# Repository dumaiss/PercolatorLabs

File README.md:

# Percolator Labs

**Homebrew Multimedia Cards for Retro Coffee-Themed Computers**

## About Percolator Labs

Percolator Labs is a collection of custom multimedia expansion cards (graphics and audio) designed for the **pBITz** series of homebrew retro computers.

Just like a perfect cup of coffee, these cards deliver rich visuals, deep sound, and satisfying performance — freshly brewed on the hardware bus.

**Tagline:**  
**"Brewed Pixels. Brewed Beats. One Perfect Cup."**

## Philosophy

- **Thematic Consistency**: Every card name follows a coffee hierarchy, from simple drip to complex crafted experiences.
- **Progressive Enhancement**: Cards scale in capability matching the host machines — from Z80 classics to 68k powerhouses.
- **Homebrew Spirit**: Designed for fun, experimentation, and maximum retro enjoyment.

---

These cards are designed specifically for the **pBITz** series of coffee-themed homebrew machines.

## Percolator Pixel — Graphics Cards

**Series Tagline:** "Freshly Rendered Graphics"

| Card | Name                        | Hardware Highlights                                      | Recommended For          | Tagline                                      |
|------|-----------------------------|----------------------------------------------------------|--------------------------|----------------------------------------------|
| 0    | **Virtual Drip**            |  Virtual TMS9928A via serial + RFB server                | Development / All        | "All the flavor, zero hardware."             |
| 1    | **Morning Joe**             | TMS9928A base implementation                             | Zephyr-80                | "The honest classic. No froth, just pure video." |
| 2    | **Lunch Crema**             | V9958 + 192KiB RAM                                       | Zephyr-80 / Espresso-09  | "Rich. Smooth. Upgraded."                    |
| 3    | **Afternoon Latte**         | Custom tile engine, 512KiB RAM, RX660 coprocessor, HD6445 CRTC, 640×480 256c | Espresso-09     | "Precision-crafted visuals."                 |
| 4    | **Nightly Double Shot**     | Framebuffer VDP, 2MiB RAM, RX660 coprocessor, HD63484 ACRTC, 1024×768 256c | Ristretto-68 / Nitro-30 | "Heavy caffeine for your framebuffer."       |

## Percolator Audio — Sound Cards

**Series Tagline:** "Brewed Beats"

| Card | Name                   | Hardware Highlights                                           | Recommended For          | Tagline                                           |
|------|------------------------|---------------------------------------------------------------|--------------------------|---------------------------------------------------|
| 0    | **Virtual Drip**       | Virtual SN76489 (3 voices + noise) via serial proxy          | Development / All        | "All the tone, zero silicon."                     |
| 1    | **Early Roast**        | 4× real SN76489 chips + PCM channel                          | Zephyr-80 / Espresso-09  | "Four classic chips, one pure shot."              |
| 2    | **Midday Blend**       | Yamaha real chip?                                            | Mid-range machines       | "Thick, rich, and layered."                       |
| 3    | **Twilight Mocha Mix** | Coprocessor-backed engine: up to 8 channels / 3-op FM + PCM  | Ristretto-68 / Nitro-30  | "Coprocessor-crafted audio art."                  |

## Roadmap

- **Phase 1 (Current)**: Core card designs (Virtual Drip, Original Joe, Crema/Latte Art, Double Shot / Quad Crema / Latte Symphony)
- **Phase 2**: Complete schematics, KiCad files, and firmware for all cards
- **Phase 3**: Driver development for Nitros-9, custom OS on 68k machines, and demo software
- **Phase 4**: Full documentation, programming manuals, and artwork (stickers, faceplates)
- **Phase 5**: Community releases, possible physical runs, and expansion ideas (e.g. higher-res cards, MIDI, etc.)

## Project Goals

- Create a cohesive multimedia ecosystem for homebrew 8/16-bit machines.
- Maintain strong coffee + retro computing theming.
- Provide high-quality, well-documented hardware and software interfaces.
- Encourage community contributions and forks.

## Repository Structure (Planned)

```
Percolator-Labs/
├── docs/                  # Schematics, manuals, programming guides
├── hardware/
│   ├── pixel/             # Graphics card designs
│   └── audio/             # Sound card designs
├── firmware/              # FPGA code, drivers
├── software/              # OS drivers (Nitros-9, custom OS, etc.)
├── artwork/               # Logos, stickers, silkscreens
└── README.md
```

## Getting Started

1. Browse the `hardware/` directory for schematics and KiCad files.
2. Check `docs/` for card-specific programming manuals.
3. Join the discussion on your favorite retro forum (or open an Issue here).

## License

This is a homebrew / open hardware project. All designs are released under the **Creative Commons Attribution-ShareAlike 4.0** license unless otherwise noted.

---

**Brewed with passion in the home lab.**  
☕ **Percolator Labs** — Making retro computing taste better since 2026.

---

*Last updated: June 2026*  
*Made for the pBITz family of homebrew machines.*

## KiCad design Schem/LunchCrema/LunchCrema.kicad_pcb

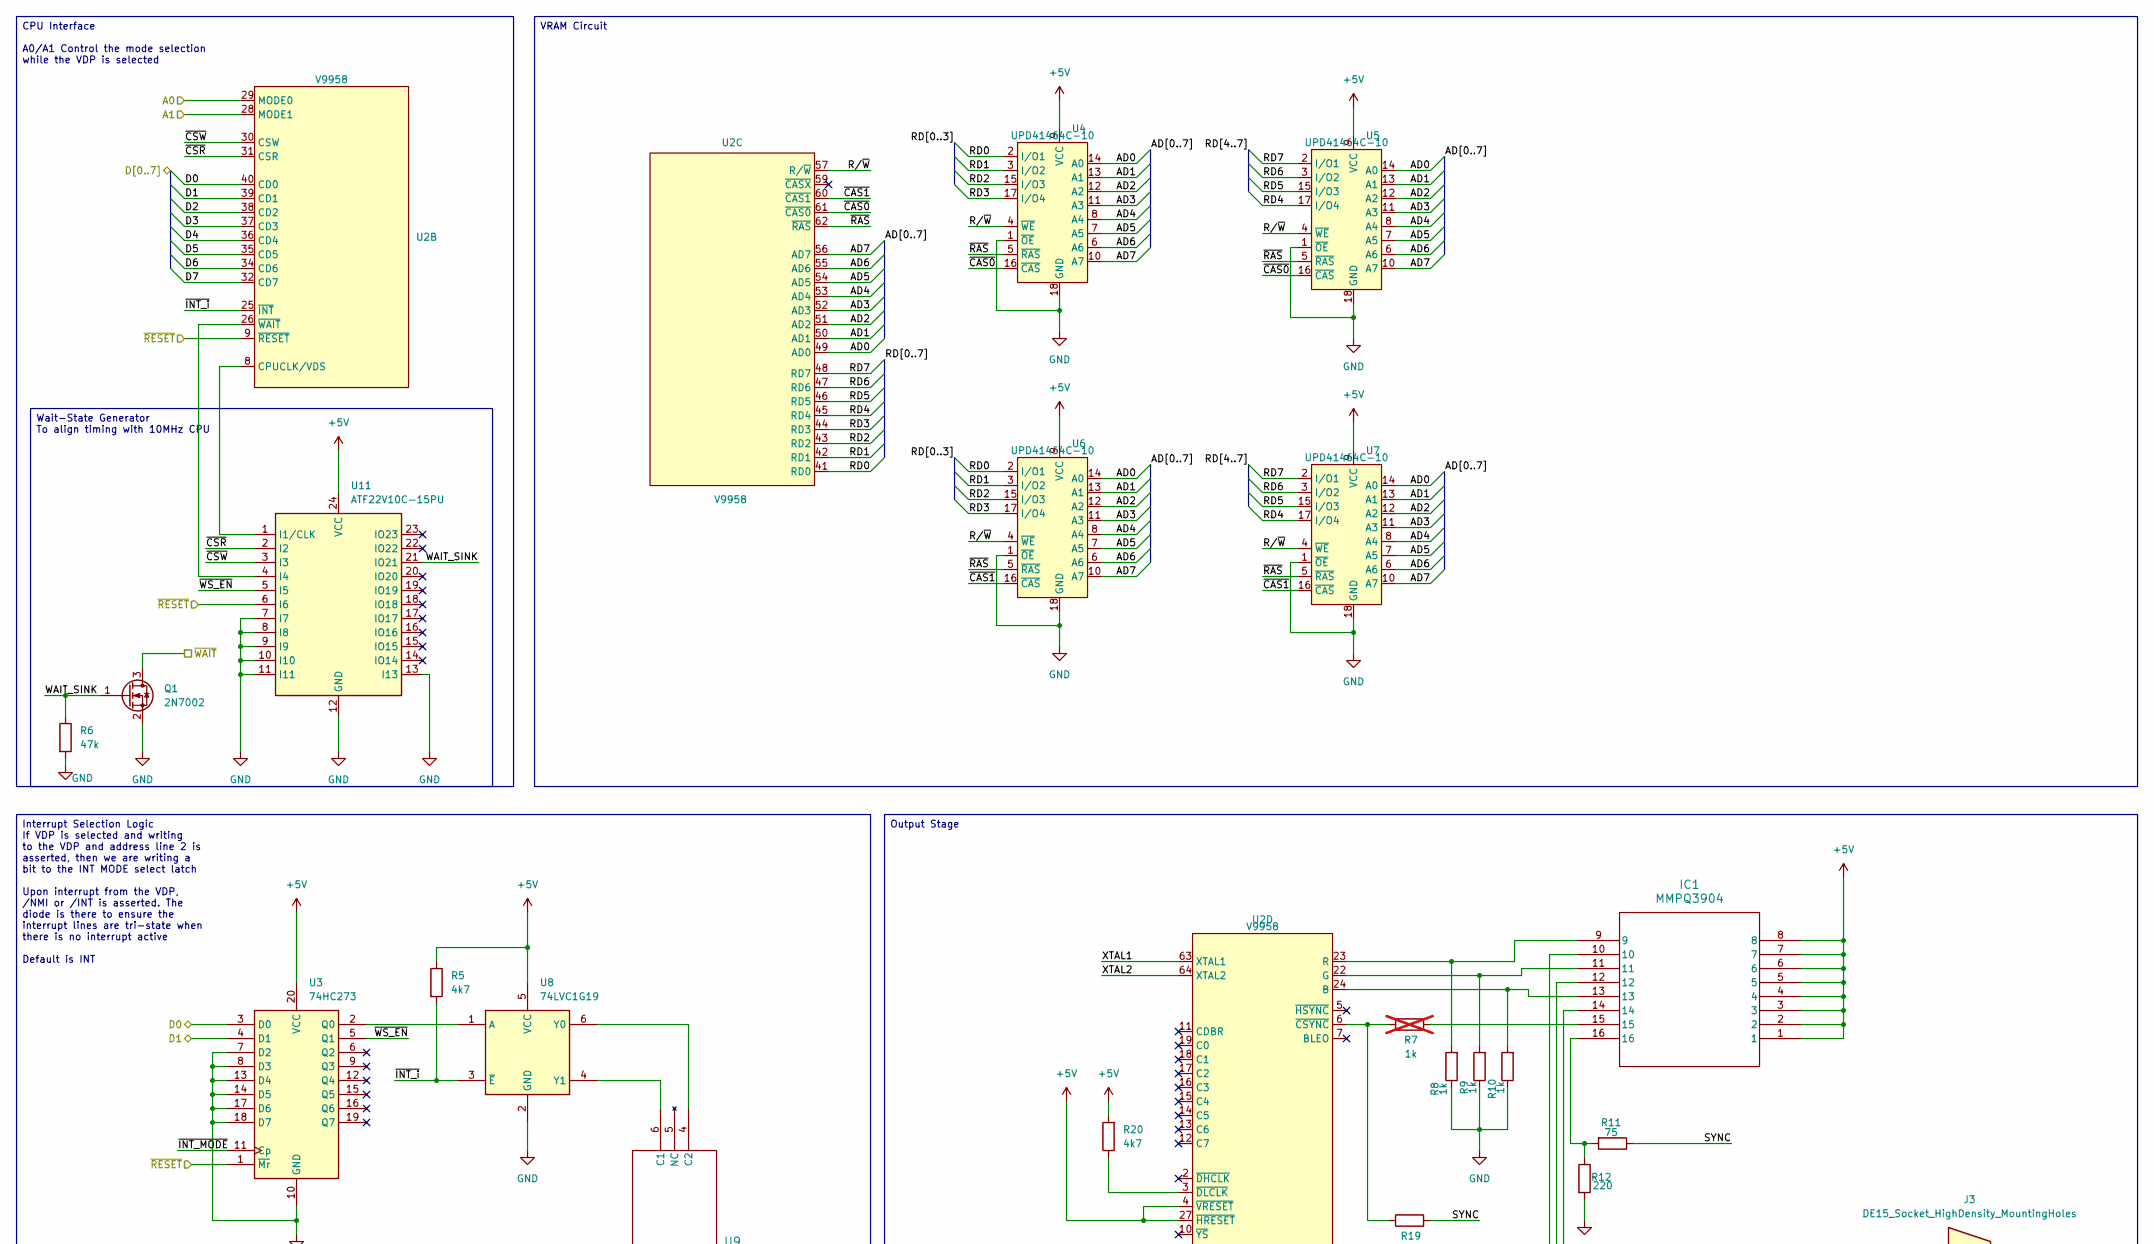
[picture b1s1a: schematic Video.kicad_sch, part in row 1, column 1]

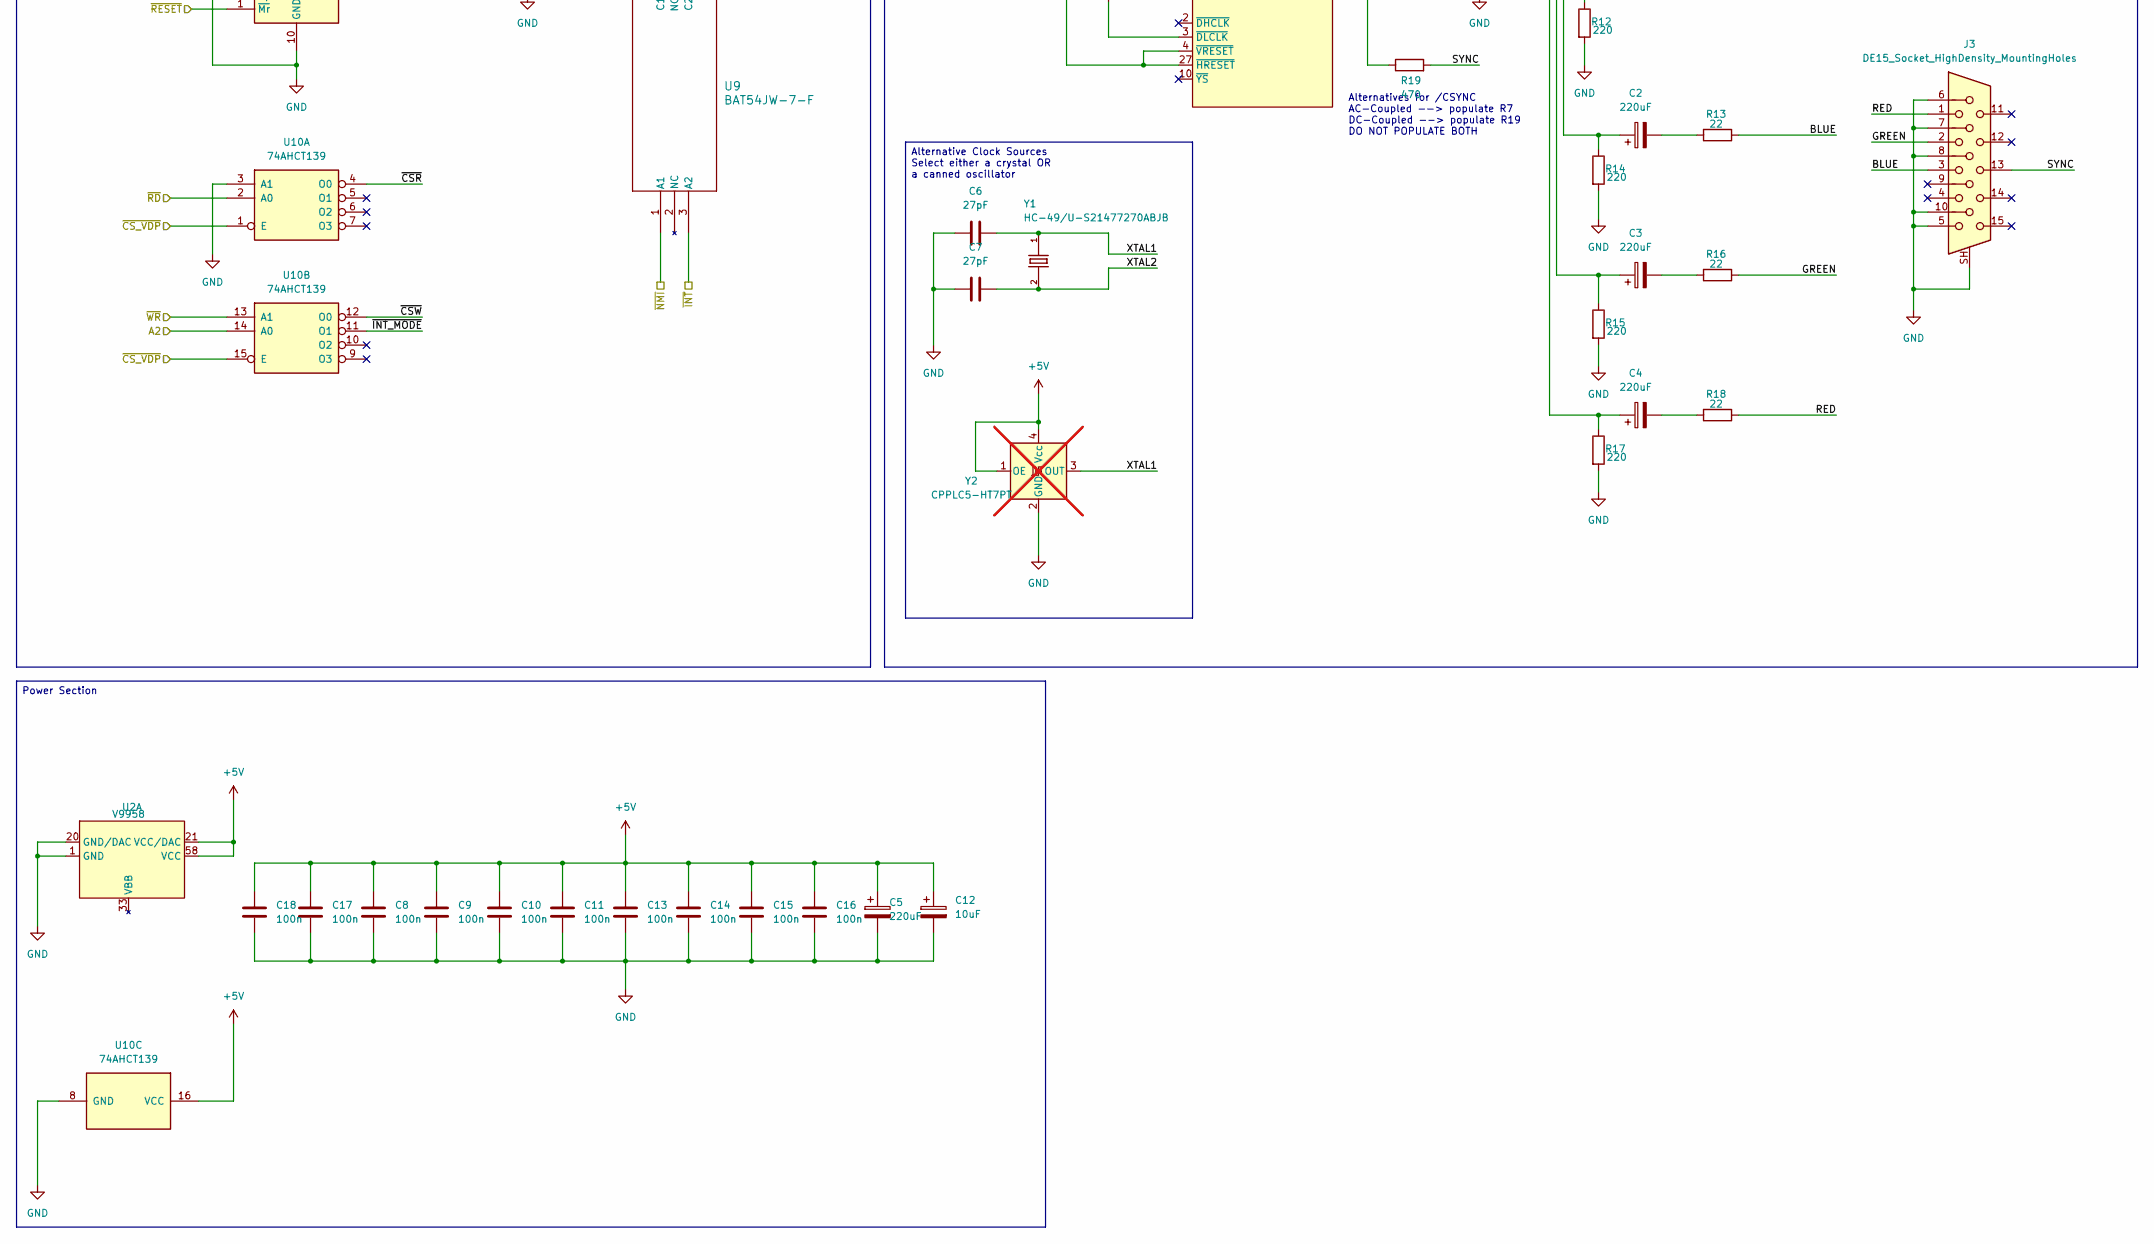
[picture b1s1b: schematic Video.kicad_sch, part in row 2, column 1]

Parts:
C2, C3, C4, C5: 220uF; CP_Radial_D6.3mm_P2.50mm; MANUFACTURER_PART_NUMBER 16YXJ220M6.3X11s
C6, C7: 27pF; C_0603_1608Metric; MANUFACTURER_PART_NUMBER VJ0603A270JXJPW1BC
C8, C9, C10, C11, C13, C14, C15, C16, C17, C18: 100n; C_0603_1608Metric; MANUFACTURER_PART_NUMBER C0603C104K5RACTU
C12: 10uF; CP_Radial_D5.0mm_P2.50mm; MANUFACTURER_PART_NUMBER EEA-GA1E100H
IC1: MMPQ3904; SOIC16_3P9X9P9_ONS; MANUFACTURER_PART_NUMBER MMPQ3904
J3: DE15_Socket_HighDensity_MountingHoles; DSUB-15-HD_Socket_Horizontal_P2.29x2.54mm_EdgePinOffset8.35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; MANUFACTURER_PART_NUMBER L77HDE15SD1CH4FVGA
Q1: 2N7002; SOT-23; MANUFACTURER_PART_NUMBER 2N7002
R5, R20: 4k7; R_0603_1608Metric; MANUFACTURER_PART_NUMBER CRCW06034K70FKEA
R6: 47k; R_0603_1608Metric; MANUFACTURER_PART_NUMBER CRCW060347K0FKEA
R7: 1k; R_0603_1608Metric; MANUFACTURER_PART_NUMBER CRCW06031K00FKEA; not fitted
R8, R9, R10: 1k; R_0603_1608Metric; MANUFACTURER_PART_NUMBER CRCW06031K00FKEA
R11: 75; R_0603_1608Metric; MANUFACTURER_PART_NUMBER CRCW060375R0FKEA
R12, R14, R15, R17: 220; R_0603_1608Metric; MANUFACTURER_PART_NUMBER CRCW0603220RJNEAHP
R13, R16, R18: 22; R_0603_1608Metric; MANUFACTURER_PART_NUMBER CRCW060322R0JNEAC
R19: 470; R_0603_1608Metric; MANUFACTURER_PART_NUMBER CRCW0603470RFKEAC
U2: V9958; D886442; MANUFACTURER_PART_NUMBER D8864-42
U3: 74HC273; SOIC-20W_7.5x12.8mm_P1.27mm; MANUFACTURER_PART_NUMBER SN74HC273DWR
U4, U5, U6, U7: UPD41464C-10; DIP-18_W7.62mm_Socket; MANUFACTURER_PART_NUMBER 1-2199298-5
U8: 74LVC1G19; SOT-363_SC-70-6; MANUFACTURER_PART_NUMBER SN74LVC1G19DCKR
U9: BAT54JW-7-F; SOT-363_SC-70-6; MANUFACTURER_PART_NUMBER BAT54JW-7-F
U10: 74AHCT139; SOIC-16_3.9x9.9mm_P1.27mm; MANUFACTURER_PART_NUMBER SN74AHCT139DR
U11: ATF22V10C-15PU; DIP-24_W7.62mm_Socket; MANUFACTURER_PART_NUMBER 1-2199298-8
Y1: HC-49/U-S21477270ABJB; XTAL_ECS-221-S-4X; MANUFACTURER_PART_NUMBER HC-49/U-S21477270ABJB
Y2: CPPLC5-HT7PT; Oscillator_SMD_SeikoEpson_SG8002CA-4Pin_7.0x5.0mm; MANUFACTURER_PART_NUMBER CPPLC5-HT7PT; not fitted

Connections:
+5V: C5.1, C8.1, C9.1, C10.1, C11.1, C12.1, C13.1, C14.1, C15.1, C16.1, C17.1, C18.1, IC1.1, IC1.2, IC1.3, IC1.4, IC1.5, IC1.6, IC1.7, IC1.8, R5.1, R20.2, U2.4 (~VRESET), U2.21 (VCC/DAC), U2.27 (~HRESET), U2.58 (VCC), U3.20 (VCC), U4.9 (VCC), U5.9 (VCC), U6.9 (VCC), U7.9 (VCC), U8.5 (VCC), U10.16 (VCC), U11.24 (VCC), Y2.1 (OE), Y2.4 (Vcc); also elsewhere on the board
/Device Select Decode/~CS_VDP: U10.1 (E), U10.15 (E); also elsewhere on the board
/Video/A0: U2.29 (MODE0); also elsewhere on the board
/Video/A1: U2.28 (MODE1); also elsewhere on the board
/Video/A2: U10.14 (A0); also elsewhere on the board
/Video/AD0: U2.49 (AD0), U4.14 (A0), U5.14 (A0), U6.14 (A0), U7.14 (A0)
/Video/AD1: U2.50 (AD1), U4.13 (A1), U5.13 (A1), U6.13 (A1), U7.13 (A1)
/Video/AD2: U2.51 (AD2), U4.12 (A2), U5.12 (A2), U6.12 (A2), U7.12 (A2)
/Video/AD3: U2.52 (AD3), U4.11 (A3), U5.11 (A3), U6.11 (A3), U7.11 (A3)
/Video/AD4: U2.53 (AD4), U4.8 (A4), U5.8 (A4), U6.8 (A4), U7.8 (A4)
/Video/AD5: U2.54 (AD5), U4.7 (A5), U5.7 (A5), U6.7 (A5), U7.7 (A5)
/Video/AD6: U2.55 (AD6), U4.6 (A6), U5.6 (A6), U6.6 (A6), U7.6 (A6)
/Video/AD7: U2.56 (AD7), U4.10 (A7), U5.10 (A7), U6.10 (A7), U7.10 (A7)
/Video/BLUE: J3.3, R13.1
/Video/D0: U2.40 (CD0), U3.3 (D0); also elsewhere on the board
/Video/D1: U2.39 (CD1), U3.4 (D1); also elsewhere on the board
/Video/D2: U2.38 (CD2); also elsewhere on the board
/Video/D3: U2.37 (CD3); also elsewhere on the board
/Video/D4: U2.36 (CD4); also elsewhere on the board
/Video/D5: U2.35 (CD5); also elsewhere on the board
/Video/D6: U2.34 (CD6); also elsewhere on the board
/Video/D7: U2.32 (CD7); also elsewhere on the board
/Video/GREEN: J3.2, R16.1
/Video/RD0: U2.41 (RD0), U4.2 (I/O1), U6.2 (I/O1)
/Video/RD1: U2.42 (RD1), U4.3 (I/O2), U6.3 (I/O2)
/Video/RD2: U2.43 (RD2), U4.15 (I/O3), U6.15 (I/O3)
/Video/RD3: U2.44 (RD3), U4.17 (I/O4), U6.17 (I/O4)
/Video/RD4: U2.45 (RD4), U5.17 (I/O4), U7.17 (I/O4)
/Video/RD5: U2.46 (RD5), U5.15 (I/O3), U7.15 (I/O3)
/Video/RD6: U2.47 (RD6), U5.3 (I/O2), U7.3 (I/O2)
/Video/RD7: U2.48 (RD7), U5.2 (I/O1), U7.2 (I/O1)
/Video/RED: J3.1, R18.1
/Video/R/~W: U2.57 (R/~W), U4.4 (~WE), U5.4 (~WE), U6.4 (~WE), U7.4 (~WE)
/Video/SYNC: J3.13, R11.1, R19.2
/Video/WAIT_SINK: Q1.1 (G), R6.1, U11.21 (IO21)
/Video/XTAL1: C6.2, U2.63 (XTAL1), Y1.1, Y2.3 (OUT)
/Video/XTAL2: C7.2, U2.64 (XTAL2), Y1.2
/Video/~CAS0: U2.61 (~CAS0), U4.16 (~CAS), U5.16 (~CAS)
/Video/~CAS1: U2.60 (~CAS1), U6.16 (~CAS), U7.16 (~CAS)
/Video/~CSR: U2.31 (CSR), U10.4 (O0), U11.2 (I2)
/Video/~CSW: U2.30 (CSW), U10.12 (O0), U11.3 (I3)
/Video/~INT_MODE: U3.11 (Cp), U10.11 (O1)
/Video/~INT_i: R5.2, U2.25 (~INT), U8.3 (~E)
/Video/~INT: U9.3 (A2); also elsewhere on the board
/Video/~NMI: U9.1 (A1); also elsewhere on the board
/Video/~RAS: U2.62 (~RAS), U4.5 (~RAS), U5.5 (~RAS), U6.5 (~RAS), U7.5 (~RAS)
/Video/~RD: U10.2 (A0); also elsewhere on the board
/Video/~RESET: U2.9 (~RESET), U3.1 (~Mr), U11.6 (I6); also elsewhere on the board
/Video/~WAIT: Q1.3 (D); also elsewhere on the board
/Video/~WR: U10.13 (A1); also elsewhere on the board
/Video/~WS_EN: U3.5 (Q1), U11.5 (I5)
GND: C5.2, C6.1, C7.1, C8.2, C9.2, C10.2, C11.2, C12.2, C13.2, C14.2, C15.2, C16.2, C17.2, C18.2, J3.5, J3.6, J3.7, J3.8, J3.10, J3.SH, Q1.2 (S), R6.2, R8.1, R9.1, R10.1, R12.2, R14.2, R15.2, R17.2, U2.1 (GND), U2.20 (GND/DAC), U3.7 (D2), U3.8 (D3), U3.10 (GND), U3.13 (D4), U3.14 (D5), U3.17 (D6), U3.18 (D7), U4.1 (~OE), U4.18 (GND), U5.1 (~OE), U5.18 (GND), U6.1 (~OE), U6.18 (GND), U7.1 (~OE), U7.18 (GND), U8.2 (GND), U10.3 (A1), U10.8 (GND), U11.7 (I7), U11.8 (I8), U11.9 (I9), U11.10 (I10), U11.11 (I11), U11.12 (GND), U11.13 (I13), Y2.2 (GND); also elsewhere on the board
unnamed: C2.1, IC1.14, R14.1
unnamed: C2.2, R13.2
unnamed: C3.1, IC1.12, R15.1
unnamed: C3.2, R16.2
unnamed: C4.1, IC1.10, R17.1
unnamed: C4.2, R18.2
unnamed: IC1.15, R7.2
unnamed: IC1.16, R11.2, R12.1
unnamed: IC1.13, R10.2, U2.24 (B)
unnamed: IC1.11, R9.2, U2.22 (G)
unnamed: IC1.9, R8.2, U2.23 (R)
unnamed: R7.1, R19.1, U2.6 (~CSYNC)
unnamed: R20.1, U2.3 (~DLCLK)
unnamed: U3.2 (Q0), U8.1 (A)
unnamed: U8.6 (Y0), U9.4 (C2)
unnamed: U8.4 (Y1), U9.6 (C1)
unnamed: U2.8 (CPUCLK/VDS), U11.1 (I1/CLK)
unnamed: U2.26 (~WAIT), U11.4 (I4)

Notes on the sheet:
Alternatives for /CSYNC AC-Coupled --> populate R7 DC-Coupled --> populate R19 DO NOT POPULATE BOTH
Power Section
Alternative Clock Sources Select either a crystal OR a canned oscillator
CPU Interface A0/A1 Control the mode selection while the VDP is selected
Output Stage
VRAM Circuit
Wait-State Generator To align timing with 10MHz CPU
Interrupt Selection Logic If VDP is selected and writing to the VDP and address line 2 is asserted, then we are writing a bit to the INT MODE select latch Upon interrupt from the VDP, /NMI or /INT is asserted. The diode is there to ensure the interrupt lines are tri-state when there is no interrupt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

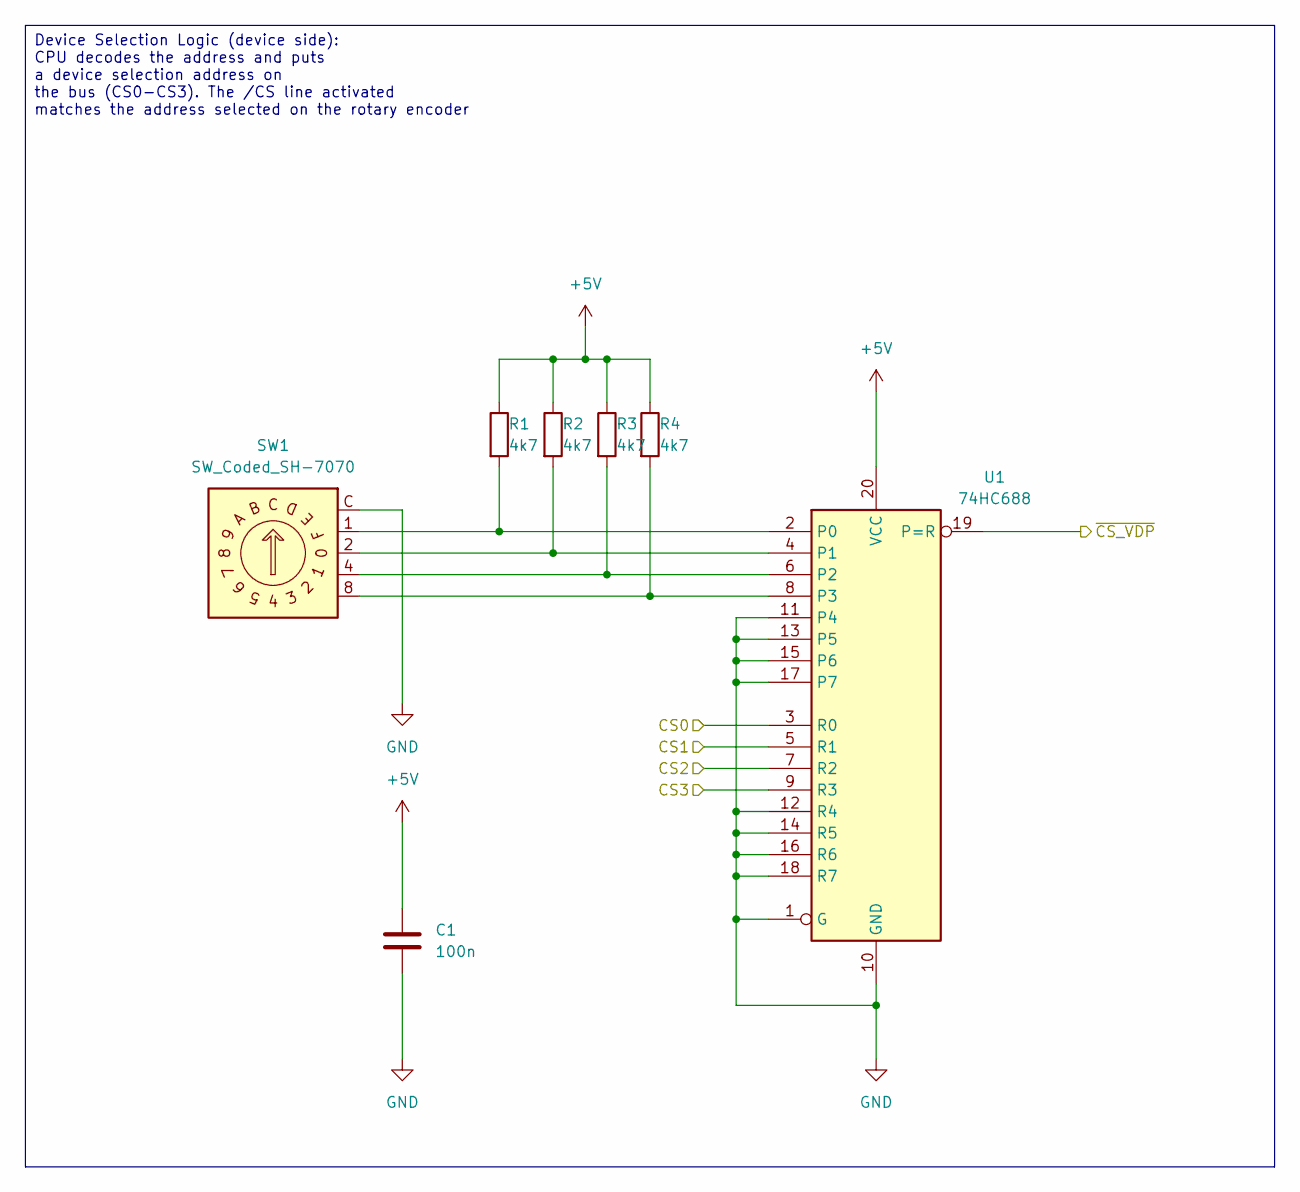
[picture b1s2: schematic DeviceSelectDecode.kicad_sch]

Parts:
C1: 100n; C_0603_1608Metric; MANUFACTURER_PART_NUMBER C0603C104K5RACTU
R1, R2, R3, R4: 4k7; R_0603_1608Metric; MANUFACTURER_PART_NUMBER CRCW06034K70FKEA
SW1: SW_Coded_SH-7070; Nidec_Copal_SH-7010C; MANUFACTURER_PART_NUMBER SH-7070MC
U1: 74HC688; TSSOP-20_4.4x6.5mm_P0.65mm; MANUFACTURER_PART_NUMBER SN74HC688PWR

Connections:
+5V: C1.1, R1.1, R2.1, R3.1, R4.1, U1.20 (VCC); also elsewhere on the board
/Device Select Decode/CS0: U1.3 (R0); also elsewhere on the board
/Device Select Decode/CS1: U1.5 (R1); also elsewhere on the board
/Device Select Decode/CS2: U1.7 (R2); also elsewhere on the board
/Device Select Decode/CS3: U1.9 (R3); also elsewhere on the board
/Device Select Decode/~CS_VDP: U1.19 (P=R); also elsewhere on the board
GND: C1.2, SW1.C, U1.1 (G), U1.10 (GND), U1.11 (P4), U1.12 (R4), U1.13 (P5), U1.14 (R5), U1.15 (P6), U1.16 (R6), U1.17 (P7), U1.18 (R7); also elsewhere on the board
unnamed: R1.2, SW1.1, U1.2 (P0)
unnamed: R2.2, SW1.2, U1.4 (P1)
unnamed: R3.2, SW1.4, U1.6 (P2)
unnamed: R4.2, SW1.8, U1.8 (P3)

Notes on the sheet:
Device Selection Logic (device side): CPU decodes the address and puts a device selection address on the bus (CS0-CS3). The /CS line activated matches the address selected on the rotary encoder

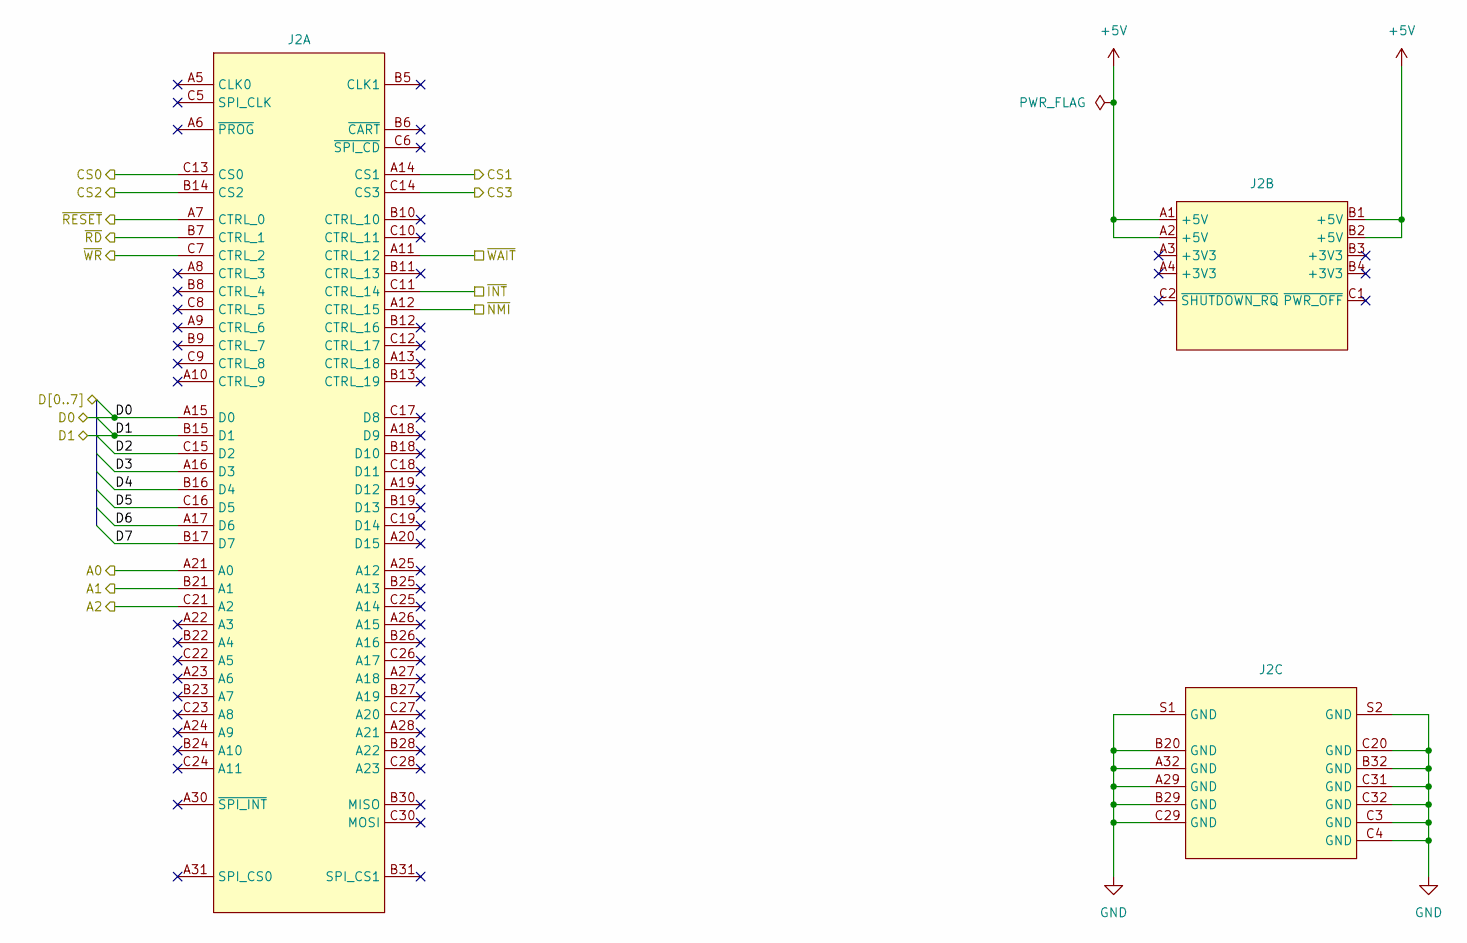
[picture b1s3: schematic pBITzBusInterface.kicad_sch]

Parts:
J2: AMPHENOL_86093967113T55F1LF; MANUFACTURER_PART_NUMBER 86093967113T55F1LF

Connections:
+5V: J2.A1 (+5V), J2.A2 (+5V), J2.B1 (+5V), J2.B2 (+5V); also elsewhere on the board
/Device Select Decode/CS0: J2.C13 (CS0); also elsewhere on the board
/Device Select Decode/CS1: J2.A14 (CS1); also elsewhere on the board
/Device Select Decode/CS2: J2.B14 (CS2); also elsewhere on the board
/Device Select Decode/CS3: J2.C14 (CS3); also elsewhere on the board
/Video/A0: J2.A21 (A0); also elsewhere on the board
/Video/A1: J2.B21 (A1); also elsewhere on the board
/Video/A2: J2.C21 (A2); also elsewhere on the board
/Video/D0: J2.A15 (D0); also elsewhere on the board
/Video/D1: J2.B15 (D1); also elsewhere on the board
/Video/D2: J2.C15 (D2); also elsewhere on the board
/Video/D3: J2.A16 (D3); also elsewhere on the board
/Video/D4: J2.B16 (D4); also elsewhere on the board
/Video/D5: J2.C16 (D5); also elsewhere on the board
/Video/D6: J2.A17 (D6); also elsewhere on the board
/Video/D7: J2.B17 (D7); also elsewhere on the board
/Video/~INT: J2.C11 (CTRL_14); also elsewhere on the board
/Video/~NMI: J2.A12 (CTRL_15); also elsewhere on the board
/Video/~RD: J2.B7 (CTRL_1); also elsewhere on the board
/Video/~RESET: J2.A7 (CTRL_0); also elsewhere on the board
/Video/~WAIT: J2.A11 (CTRL_12); also elsewhere on the board
/Video/~WR: J2.C7 (CTRL_2); also elsewhere on the board
GND: J2.A29 (GND), J2.A32 (GND), J2.B20 (GND), J2.B29 (GND), J2.B32 (GND), J2.C3 (GND), J2.C4 (GND), J2.C20 (GND), J2.C29 (GND), J2.C31 (GND), J2.C32 (GND), J2.S1 (GND), J2.S2 (GND); also elsewhere on the board

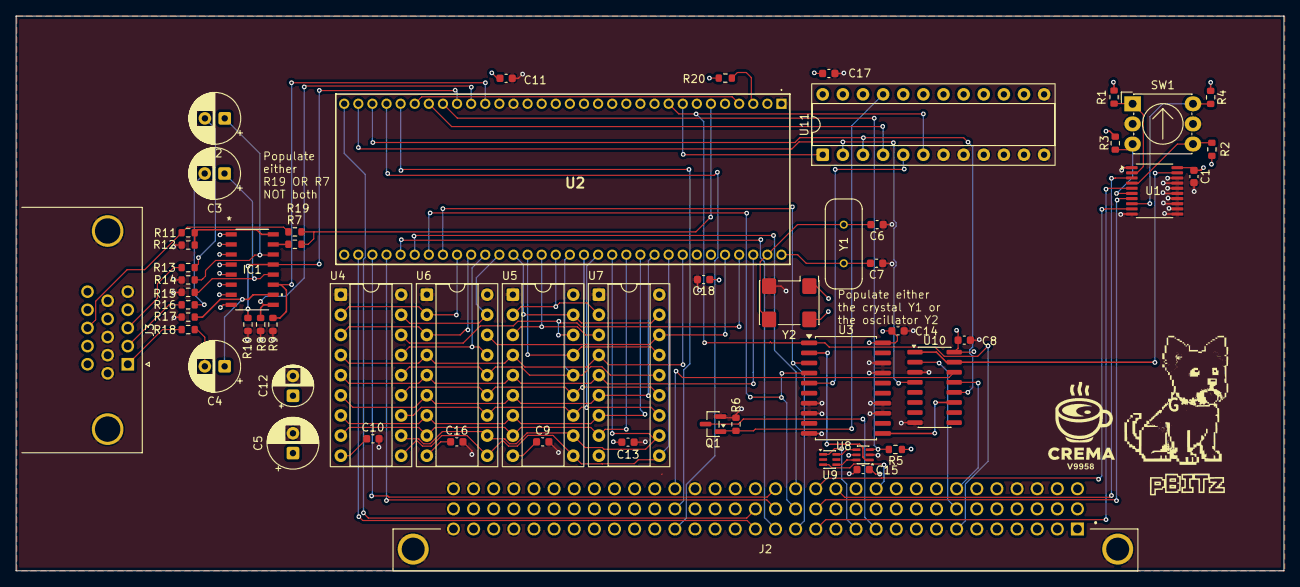
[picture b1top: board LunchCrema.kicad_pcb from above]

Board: 6 copper layers, 160.0 x 70.0 mm, 56 parts (0 on the bottom side), 78 nets.

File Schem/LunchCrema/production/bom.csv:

Designator,Footprint,Quantity,Value,LCSC Part #
"C1, C10, C11, C13, C14, C15, C16, C17, C18, C8, C9",0603,11,100n,
C12,CP_Radial_D5.0mm_P2.50mm,1,10uF,
"C2, C3, C4, C5",CP_Radial_D6.3mm_P2.50mm,4,220uF,
"C6, C7",0603,2,27pF,
IC1,SOIC16_3P9X9P9_ONS,1,MMPQ3904,
J2,AMPHENOL_86093967113T55F1LF,1,~,
J3,DSUB-15-HD_Socket_Horizontal_P2.29x2.54mm_EdgePinOffset8.35mm_Housed_MountingHolesOffset10.89mm,1,DE15_Socket_HighDensity_MountingHoles,
Q1,SOT-23,1,2N7002,
"R1, R2, R20, R3, R4, R5",0603,6,4k7,
"R10, R8, R9",0603,3,1k,
R11,0603,1,75,
"R12, R14, R15, R17",0603,4,220,
"R13, R16, R18",0603,3,22,
R19,0603,1,470,
R6,0603,1,47k,
SW1,Nidec_Copal_SH-7010C,1,SW_Coded_SH-7070,
U1,TSSOP-20_4.4x6.5mm_P0.65mm,1,74HC688,
U10,SOIC-16_3.9x9.9mm_P1.27mm,1,74AHCT139,
U11,DIP-24_W7.62mm_Socket,1,ATF22V10C-15PU,
U2,D886442,1,V9958,
U3,SOIC-20W_7.5x12.8mm_P1.27mm,1,74HC273,
"U4, U5, U6, U7",DIP-18_W7.62mm_Socket,4,UPD41464C-10,
U8,SOT-363_SC-70-6,1,74LVC1G19,
U9,SOT-363_SC-70-6,1,BAT54JW-7-F,
Y1,XTAL_ECS-221-S-4X,1,HC-49/U-S21477270ABJB,

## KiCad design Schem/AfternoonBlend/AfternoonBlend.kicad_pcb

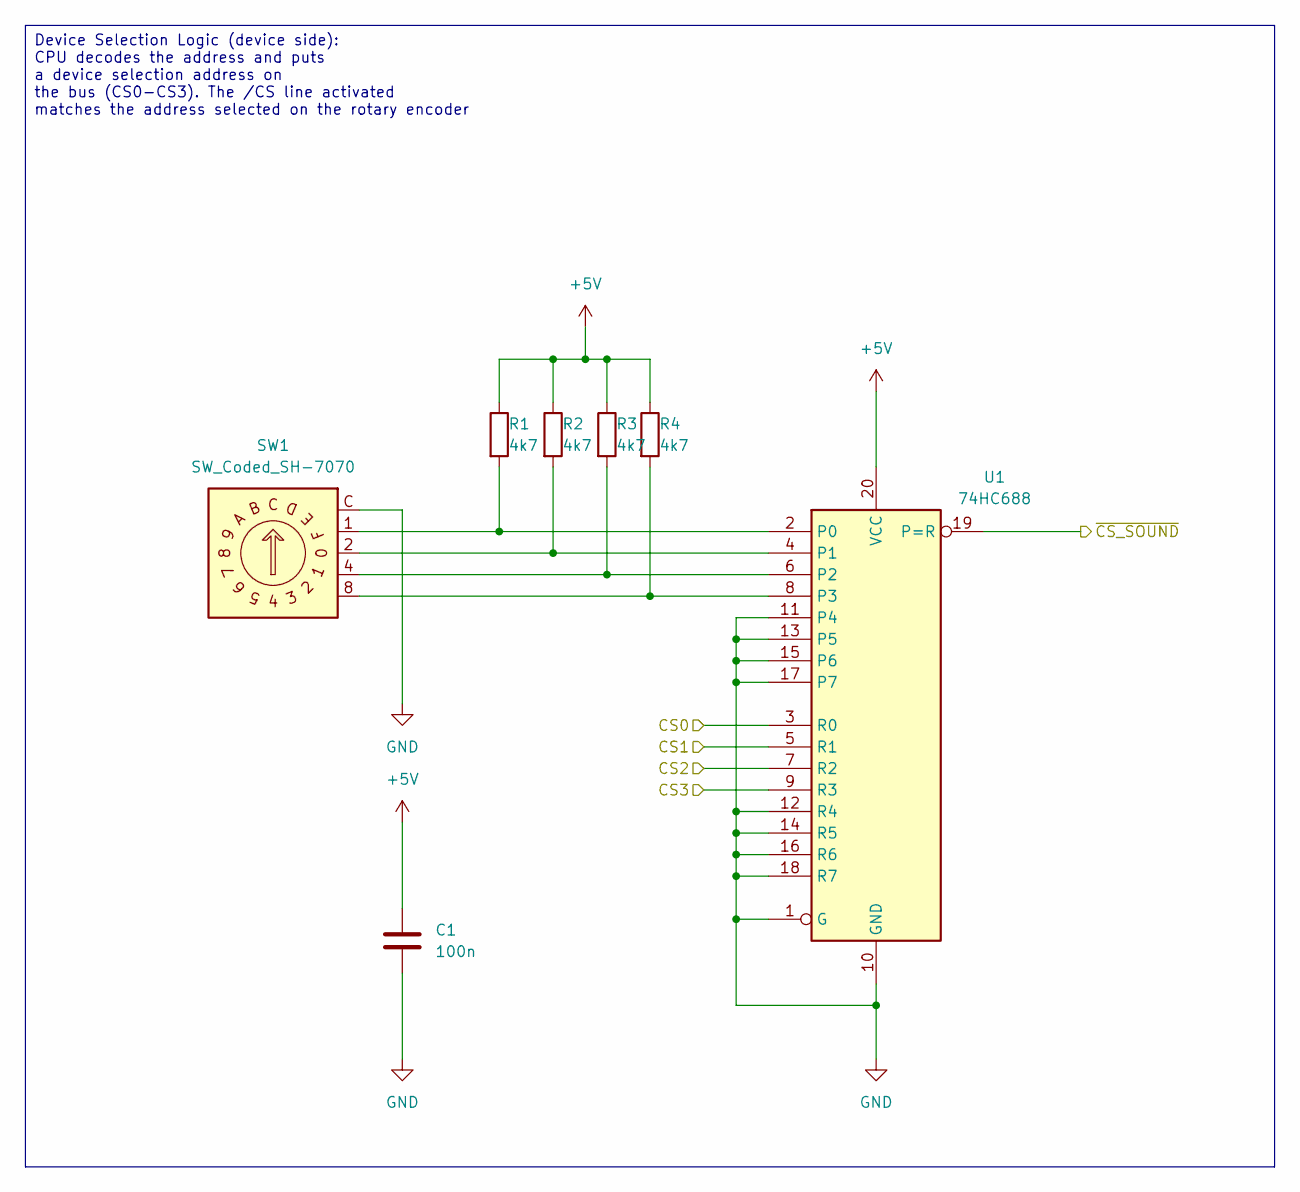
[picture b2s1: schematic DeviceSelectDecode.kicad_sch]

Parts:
C1: 100n; C_0603_1608Metric; MANUFACTURER_PART_NUMBER C0603C104K5RACTU
R1, R2, R3, R4: 4k7; R_0603_1608Metric; MANUFACTURER_PART_NUMBER CRCW06034K70FKEA
SW1: SW_Coded_SH-7070; Nidec_Copal_SH-7010C; MANUFACTURER_PART_NUMBER SH-7070MC
U1: 74HC688; TSSOP-20_4.4x6.5mm_P0.65mm; MANUFACTURER_PART_NUMBER SN74HC688PWR

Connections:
+5V: C1.1, R1.1, R2.1, R3.1, R4.1, U1.20 (VCC); also elsewhere on the board
/Device Select Decode/CS0: U1.3 (R0); also elsewhere on the board
/Device Select Decode/CS1: U1.5 (R1); also elsewhere on the board
/Device Select Decode/CS2: U1.7 (R2); also elsewhere on the board
/Device Select Decode/CS3: U1.9 (R3); also elsewhere on the board
/Device Select Decode/~CS_SOUND: U1.19 (P=R); also elsewhere on the board
GND: C1.2, SW1.C, U1.1 (G), U1.10 (GND), U1.11 (P4), U1.12 (R4), U1.13 (P5), U1.14 (R5), U1.15 (P6), U1.16 (R6), U1.17 (P7), U1.18 (R7); also elsewhere on the board
unnamed: R1.2, SW1.1, U1.2 (P0)
unnamed: R2.2, SW1.2, U1.4 (P1)
unnamed: R3.2, SW1.4, U1.6 (P2)
unnamed: R4.2, SW1.8, U1.8 (P3)

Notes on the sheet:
Device Selection Logic (device side): CPU decodes the address and puts a device selection address on the bus (CS0-CS3). The /CS line activated matches the address selected on the rotary encoder

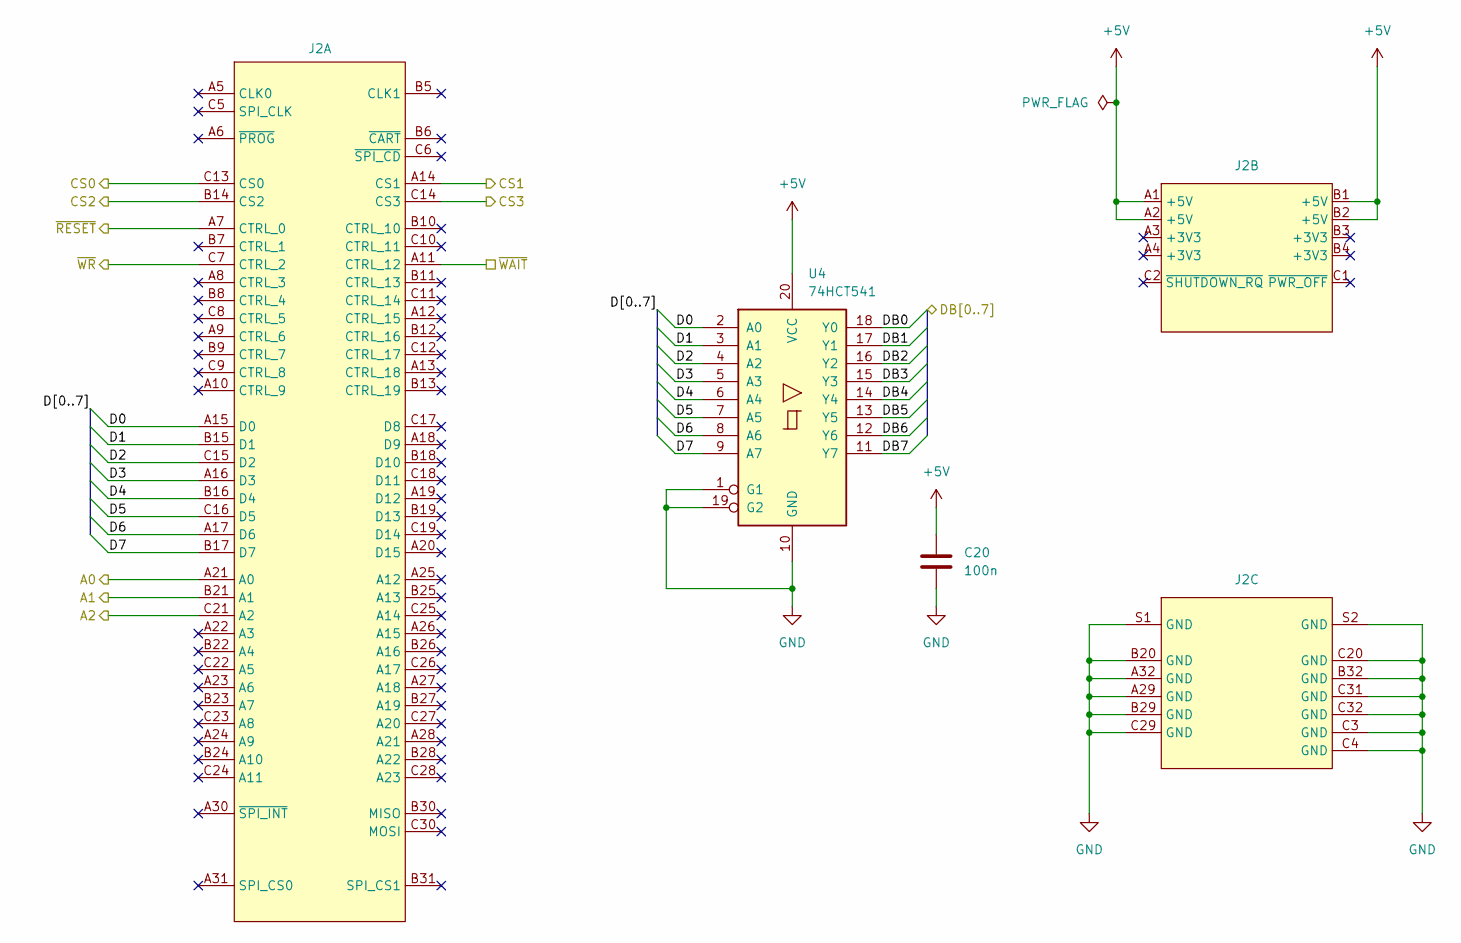
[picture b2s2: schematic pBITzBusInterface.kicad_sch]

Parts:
C20: 100n; C_0603_1608Metric; MANUFACTURER_PART_NUMBER C0603C104K5RACTU
J2: AMPHENOL_86093967113T55F1LF; MANUFACTURER_PART_NUMBER 86093967113T55F1LF
U4: 74HCT541; TSSOP-20_4.4x6.5mm_P0.65mm; MANUFACTURER_PART_NUMBER 74HCT541PW,118

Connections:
+5V: C20.1, J2.A1 (+5V), J2.A2 (+5V), J2.B1 (+5V), J2.B2 (+5V), U4.20 (VCC); also elsewhere on the board
/Device Select Decode/CS0: J2.C13 (CS0); also elsewhere on the board
/Device Select Decode/CS1: J2.A14 (CS1); also elsewhere on the board
/Device Select Decode/CS2: J2.B14 (CS2); also elsewhere on the board
/Device Select Decode/CS3: J2.C14 (CS3); also elsewhere on the board
/Sound/A0: J2.A21 (A0); also elsewhere on the board
/Sound/A1: J2.B21 (A1); also elsewhere on the board
/Sound/A2: J2.C21 (A2); also elsewhere on the board
/Sound/DB0: U4.18 (Y0); also elsewhere on the board
/Sound/DB1: U4.17 (Y1); also elsewhere on the board
/Sound/DB2: U4.16 (Y2); also elsewhere on the board
/Sound/DB3: U4.15 (Y3); also elsewhere on the board
/Sound/DB4: U4.14 (Y4); also elsewhere on the board
/Sound/DB5: U4.13 (Y5); also elsewhere on the board
/Sound/DB6: U4.12 (Y6); also elsewhere on the board
/Sound/DB7: U4.11 (Y7); also elsewhere on the board
/Sound/~RESET: J2.A7 (CTRL_0); also elsewhere on the board
/Sound/~WAIT: J2.A11 (CTRL_12); also elsewhere on the board
/Sound/~WR: J2.C7 (CTRL_2); also elsewhere on the board
/pBITz Bus Interface/D0: J2.A15 (D0), U4.2 (A0)
/pBITz Bus Interface/D1: J2.B15 (D1), U4.3 (A1)
/pBITz Bus Interface/D2: J2.C15 (D2), U4.4 (A2)
/pBITz Bus Interface/D3: J2.A16 (D3), U4.5 (A3)
/pBITz Bus Interface/D4: J2.B16 (D4), U4.6 (A4)
/pBITz Bus Interface/D5: J2.C16 (D5), U4.7 (A5)
/pBITz Bus Interface/D6: J2.A17 (D6), U4.8 (A6)
/pBITz Bus Interface/D7: J2.B17 (D7), U4.9 (A7)
GND: C20.2, J2.A29 (GND), J2.A32 (GND), J2.B20 (GND), J2.B29 (GND), J2.B32 (GND), J2.C3 (GND), J2.C4 (GND), J2.C20 (GND), J2.C29 (GND), J2.C31 (GND), J2.C32 (GND), J2.S1 (GND), J2.S2 (GND), U4.1 (G1), U4.10 (GND), U4.19 (G2); also elsewhere on the board
